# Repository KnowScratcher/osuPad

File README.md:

# osu! Pad

<p align="center">I like to play osu! and probably so do you!</p>

<div align="center">
    
</div>

# BOM
Because I live in Taiwan, so I'll add a TWD column.

| Item                 | Amount | Price(USD) | Total(USD) | Total(TWD) |
| -------------------- | ------ | ---------- | ---------- | ---------- |
| XIAO-RP2040          | 1      | 7.41       | 7.41       | 219        |
| Custom PCB           | 1      | 4.00       | 4.00       | 119        |
| Cherry MX key switch | 9      | 0.37       | 3.35       | 99         |
| Cherry MX key cap    | 9      | ?          | ?          | ?          |
| 3D printed case      | 1      | 0.65       | 0.65       | 20         |
| SSD1306 0.91' oled   | 1      | 2.34       | 2.34       | 69         |
| M3x16mm screws       | 4      | 0.1        | 0.4        | 12         |
| Total                |        |            | 14.8       | 538        |

# Journal
The journal is in [JOURNAL.md](JOURNAL.md)

A brief summery of the journal:

## How it all started

I was on a meeting with hack club hackers, and I was so impressed that I decided to join them and make this thing.

## What will it do?

It's basically a small keyboard, I designed it for <a target="_blank" href="https://github.com/ppy/osu">osu</a>, with zxc keys and some moving button, and also a switch mode button to make it expandable.

# Schematic

# Licensing

This project comprises both hardware designs and software components, each licensed separately to ensure clarity and appropriate reciprocity.

## Hardware Designs (3D Models, Wiring Diagrams, etc.)

All hardware design files, including but not limited to 3D models, PCB layouts, schematic diagrams, and associated documentation, are licensed under the **CERN Open Hardware Licence Version 2 - Strongly Reciprocal (CERN-OHL-S-2.0)**.
You can find the full text of this license in [LICENSE_HARDWARE](LICENSE_HARDWARE).

## Software (Data Server, ESP32 Firmware, etc.)

All software components, including but not limited to firmware, are licensed under the **GNU Affero General Public License Version 3.0 or later (AGPL-3.0-or-later)**.
You can find the full text of this license in [LICENSE_SOFTWARE](LICENSE_SOFTWARE).

## Documentation

All documentations, including but not limited to the README.md and wiki pages, are licensed under the **CC-BY-SA-4.0**.
You can find the full text of this license in [LICENSE_DOCUMENTATION](LICENSE_DOCUMENTATION)

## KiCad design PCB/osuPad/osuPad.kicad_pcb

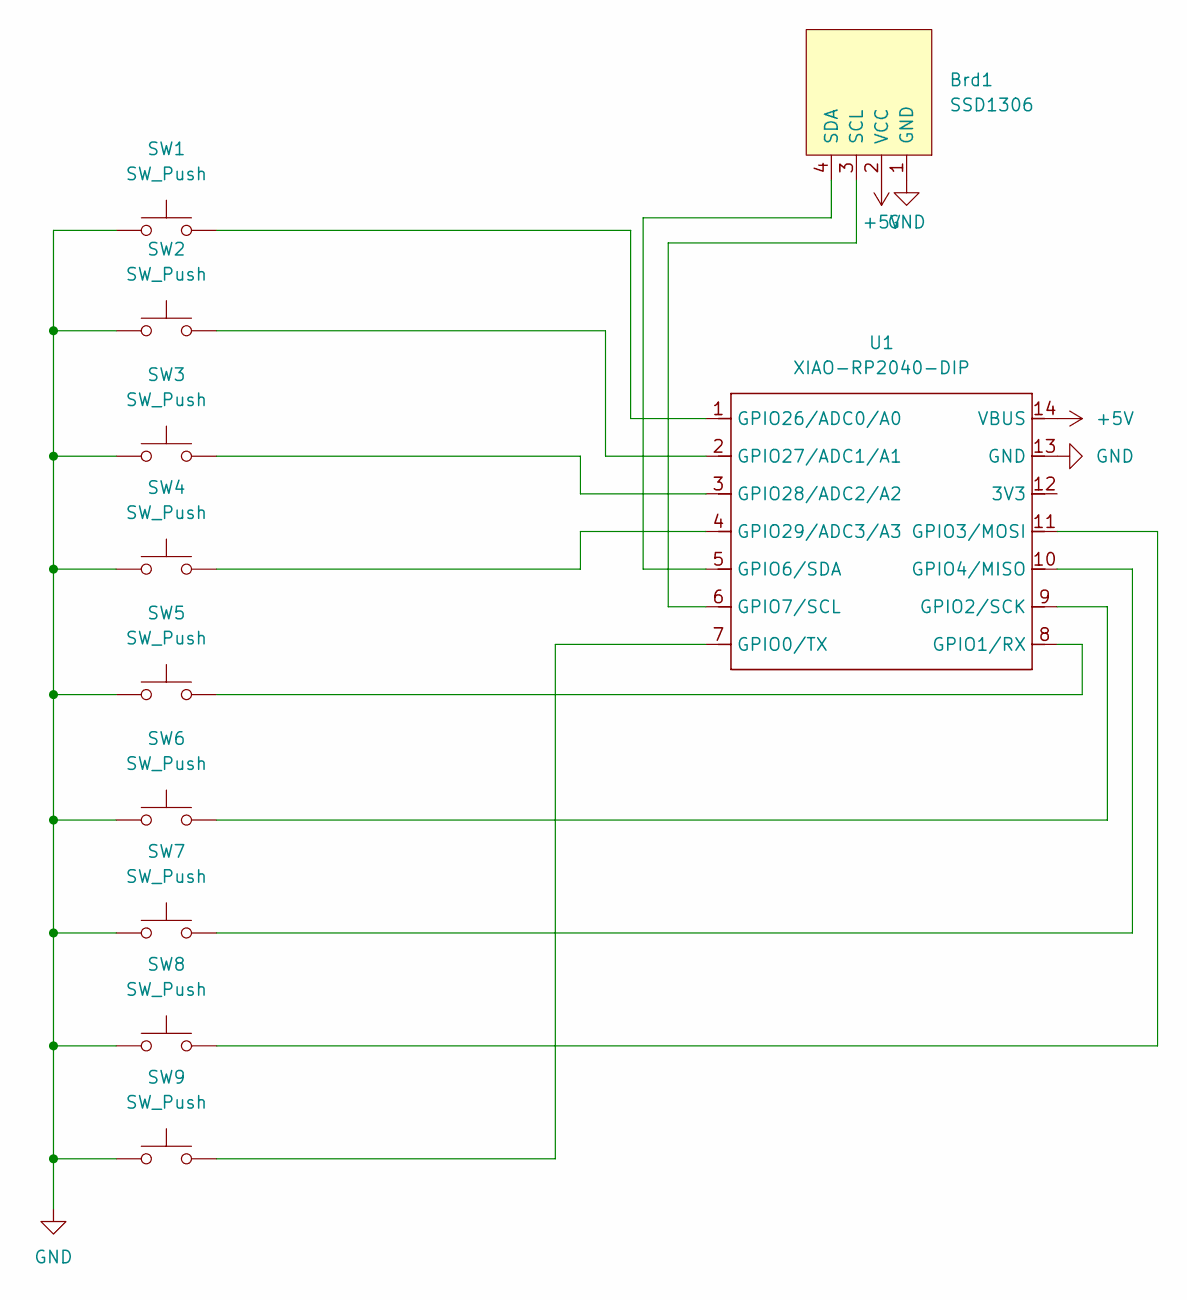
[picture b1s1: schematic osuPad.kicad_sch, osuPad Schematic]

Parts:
Brd1: SSD1306; SSD1306-0.91-OLED-4pin-128x32
SW1, SW2, SW3, SW4, SW5, SW6, SW7, SW8, SW9: SW_Push; SW_Cherry_MX_1.00u_PCB
U1: XIAO-RP2040-DIP

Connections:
+5V: Brd1.2 (VCC), U1.14 (VBUS)
GND: Brd1.1 (GND), SW1.1, SW2.1, SW3.1, SW4.1, SW5.1, SW6.1, SW7.1, SW8.1, SW9.1, U1.13 (GND)
unnamed: Brd1.3 (SCL), U1.6 (GPIO7/SCL)
unnamed: Brd1.4 (SDA), U1.5 (GPIO6/SDA)
unnamed: SW9.2, U1.7 (GPIO0/TX)
unnamed: SW5.2, U1.8 (GPIO1/RX)
unnamed: SW6.2, U1.9 (GPIO2/SCK)
unnamed: SW8.2, U1.11 (GPIO3/MOSI)
unnamed: SW7.2, U1.10 (GPIO4/MISO)
unnamed: SW1.2, U1.1 (GPIO26/ADC0/A0)
unnamed: SW2.2, U1.2 (GPIO27/ADC1/A1)
unnamed: SW3.2, U1.3 (GPIO28/ADC2/A2)
unnamed: SW4.2, U1.4 (GPIO29/ADC3/A3)

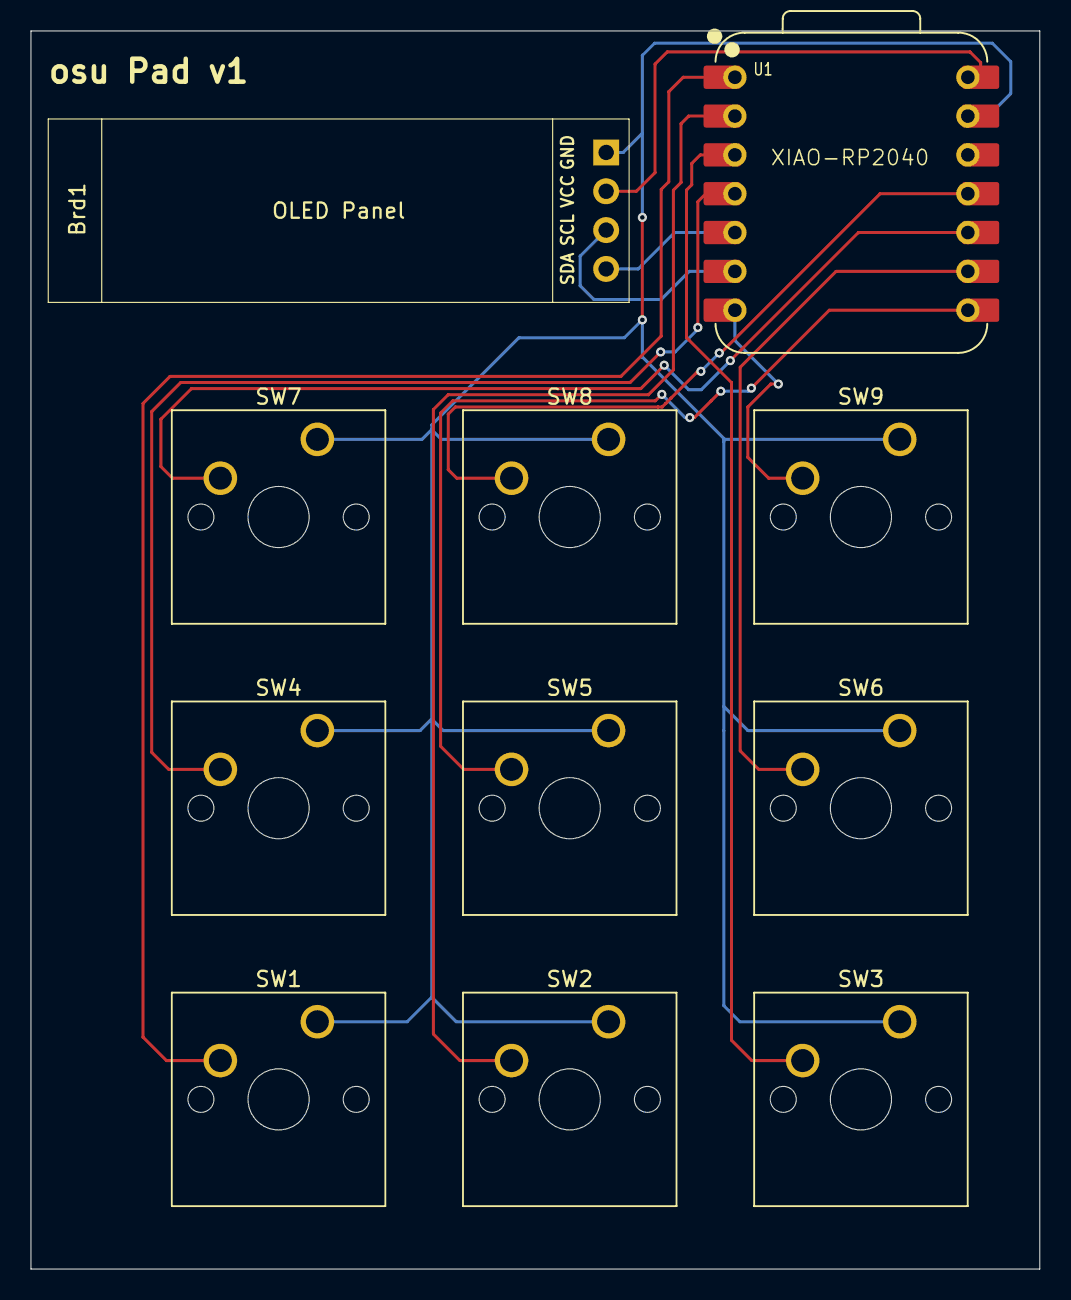
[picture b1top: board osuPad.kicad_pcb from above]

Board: 2 copper layers, 66.0 x 81.0 mm, 11 parts (0 on the bottom side), 13 nets.

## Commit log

2025-06-15 init
2025-06-15 update model and image
2025-06-15 update url
2025-06-15 update firmware
2025-06-16 update model
2025-06-16 update journal
2025-06-17 update spent time
2025-06-18 add assembly version
2025-06-18 update BOM
2025-06-21 update image
2025-06-21 update license
2025-06-22 add journal
